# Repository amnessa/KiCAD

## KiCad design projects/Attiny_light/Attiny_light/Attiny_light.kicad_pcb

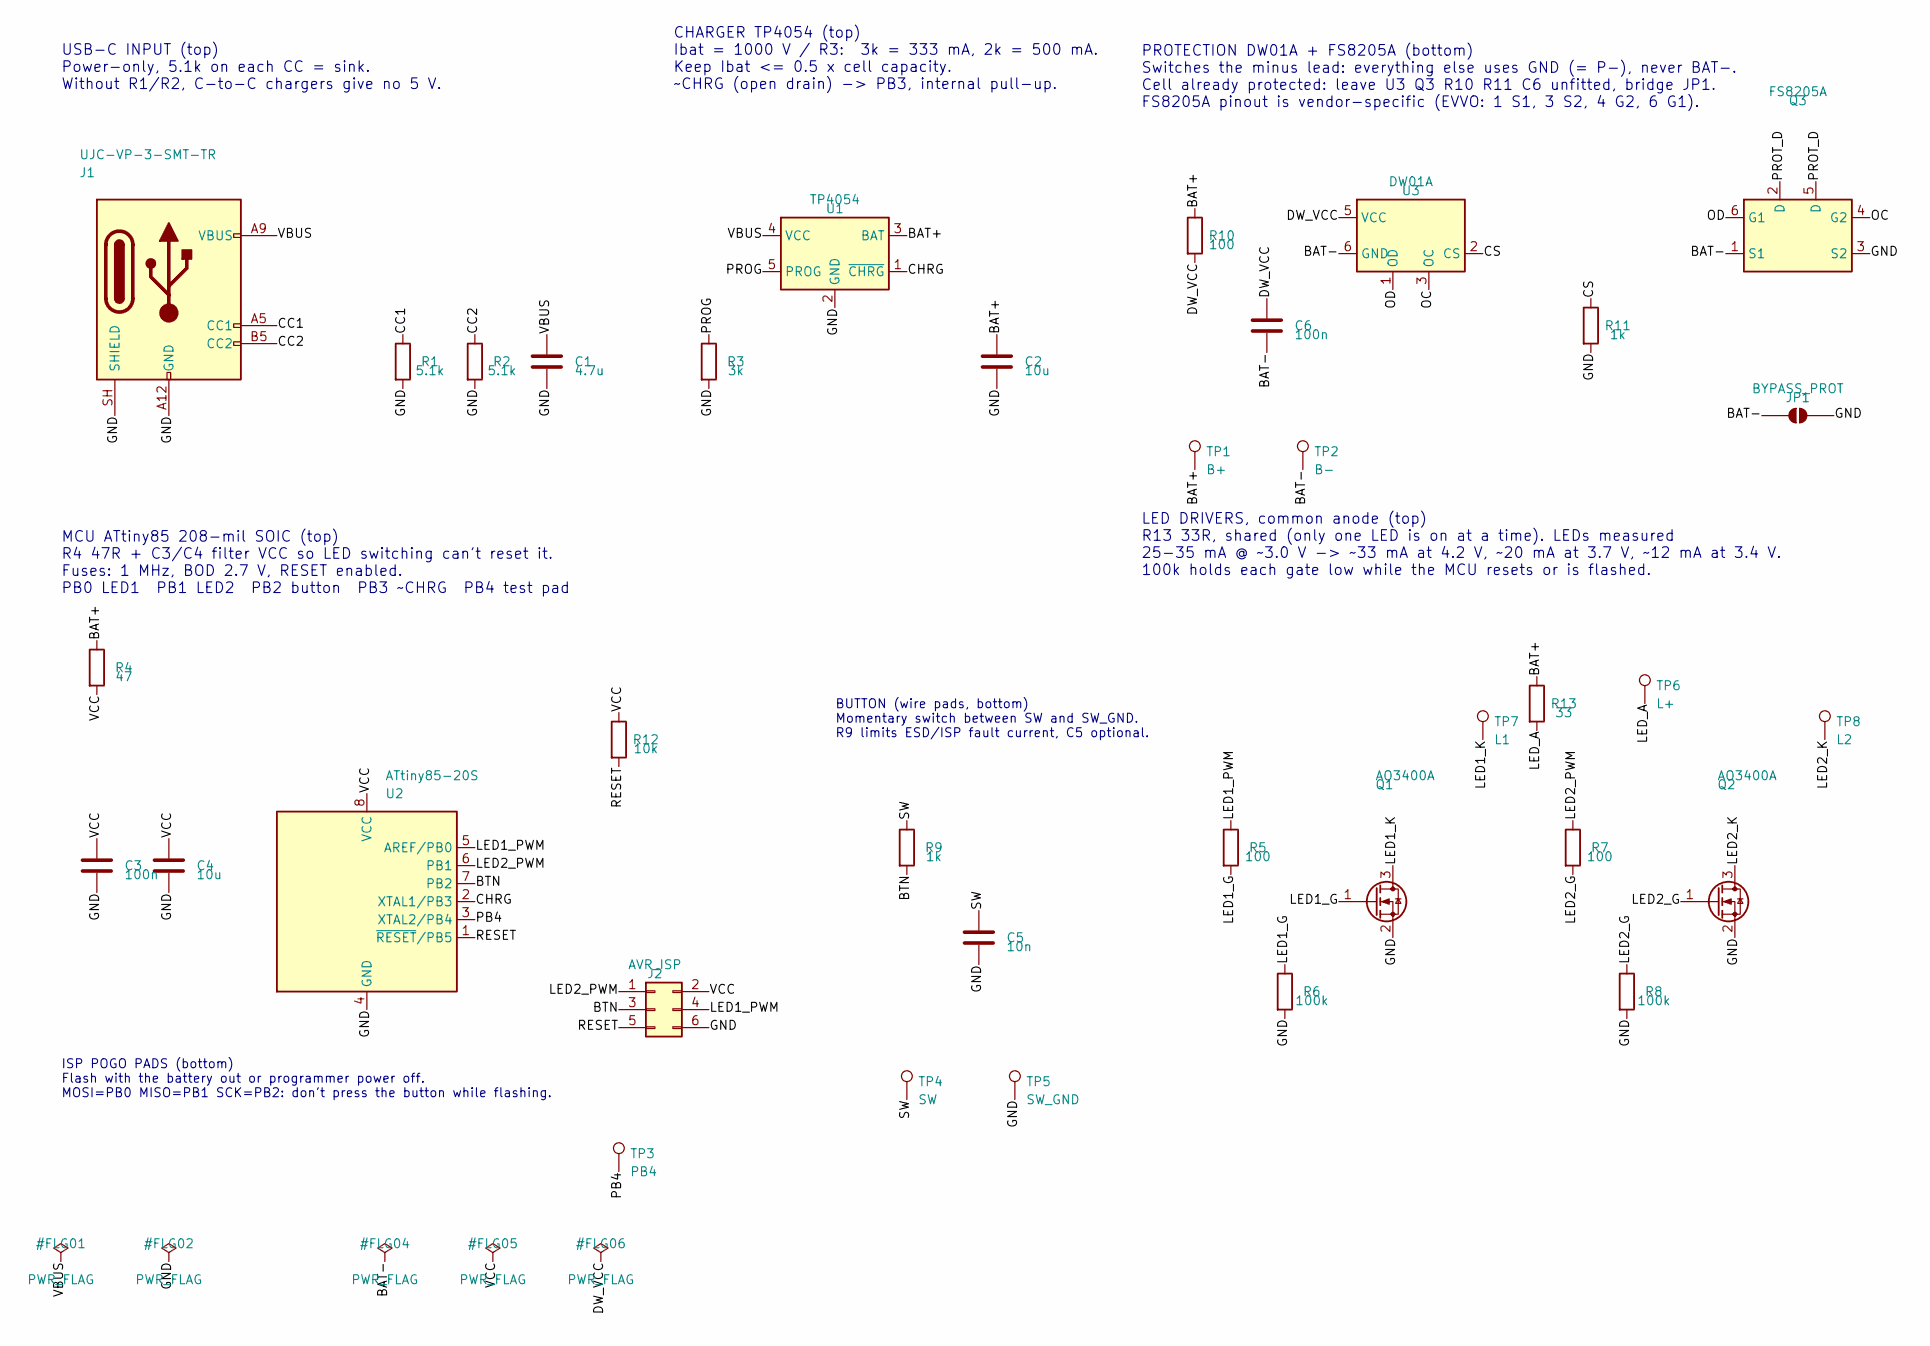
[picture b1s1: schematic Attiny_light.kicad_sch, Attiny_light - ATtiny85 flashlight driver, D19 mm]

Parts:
C1: 4.7u; C_0603_1608Metric
C2, C4: 10u; C_0603_1608Metric
C3, C6: 100n; C_0402_1005Metric
C5: 10n; C_0402_1005Metric
J1: UJC-VP-3-SMT-TR; USB_C_Receptacle_SameSky_UJC-VP-3-SMT_Vertical
J2: AVR_ISP; AVR_ISP_Pogo_2x03_P2.54mm_SMD
JP1: BYPASS_PROT; SolderJumper-2_P1.3mm_Open_RoundedPad1.0x1.5mm
Q1, Q2: AO3400A; SOT-23
Q3: FS8205A; SOT-23-6
R1, R2: 5.1k; R_0402_1005Metric
R3: 3k; R_0402_1005Metric
R4: 47; R_0402_1005Metric
R5, R7, R10: 100; R_0402_1005Metric
R6, R8: 100k; R_0402_1005Metric
R9, R11: 1k; R_0402_1005Metric
R12: 10k; R_0402_1005Metric
R13: 33; R_0603_1608Metric
TP1: B+; TestPoint_Pad_2.0x2.0mm
TP2: B-; TestPoint_Pad_2.0x2.0mm
TP3: PB4; TestPoint_Pad_D1.0mm
TP4: SW; TestPoint_Pad_1.5x1.5mm
TP5: SW_GND; TestPoint_Pad_1.5x1.5mm
TP6: L+; TestPoint_Pad_1.5x1.5mm
TP7: L1; TestPoint_Pad_1.5x1.5mm
TP8: L2; TestPoint_Pad_1.5x1.5mm
U1: TP4054; SOT-23-5
U2: ATtiny85-20S; SOIC-8_5.3x5.3mm_P1.27mm
U3: DW01A; SOT-23-6

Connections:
/BAT+: C2.1, R4.1, R10.1, R13.1, TP1.1, U1.3 (BAT)
/BAT-: C6.2, JP1.1 (A), Q3.1 (S1), TP2.1, U3.6 (GND)
/BTN: J2.3, R9.2, U2.7 (PB2)
/CC1: J1.A5 (CC1), R1.1
/CC2: J1.B5 (CC2), R2.1
/CHRG: U1.1 (~CHRG), U2.2 (XTAL1/PB3)
/CS: R11.1, U3.2 (CS)
/DW_VCC: C6.1, R10.2, U3.5 (VCC)
/GND: C1.2, C2.2, C3.2, C4.2, C5.2, J1.A12 (GND), J1.B12 (GND), J1.SH (SHIELD), J2.6, JP1.2 (B), Q1.2 (S), Q2.2 (S), Q3.3 (S2), R1.2, R2.2, R3.2, R6.2, R8.2, R11.2, TP5.1, U1.2 (GND), U2.4 (GND)
/LED1_G: Q1.1 (G), R5.2, R6.1
/LED1_K: Q1.3 (D), TP7.1
/LED1_PWM: J2.4, R5.1, U2.5 (AREF/PB0)
/LED2_G: Q2.1 (G), R7.2, R8.1
/LED2_K: Q2.3 (D), TP8.1
/LED2_PWM: J2.1, R7.1, U2.6 (PB1)
/LED_A: R13.2, TP6.1
/OC: Q3.4 (G2), U3.3 (OC)
/OD: Q3.6 (G1), U3.1 (OD)
/PB4: TP3.1, U2.3 (XTAL2/PB4)
/PROG: R3.1, U1.5 (PROG)
/PROT_D: Q3.2 (D), Q3.5 (D)
/RESET: J2.5, R12.2, U2.1 (~RESET/PB5)
/SW: C5.1, R9.1, TP4.1
/VBUS: C1.1, J1.A9 (VBUS), J1.B9 (VBUS), U1.4 (VCC)
/VCC: C3.1, C4.1, J2.2, R4.2, R12.1, U2.8 (VCC)

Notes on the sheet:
CHARGER TP4054 (top) Ibat = 1000 V / R3: 3k = 333 mA, 2k = 500 mA. Keep Ibat <= 0.5 x cell capacity. ~CHRG (open drain) -> PB3, internal pull-up.
ISP POGO PADS (bottom) Flash with the battery out or programmer power off. MOSI=PB0 MISO=PB1 SCK=PB2: don't press the button while flashing.
LED DRIVERS, common anode (top) R13 33R, shared (only one LED is on at a time). LEDs measured 25-35 mA @ ~3.0 V -> ~33 mA at 4.2 V, ~20 mA at 3.7 V, ~12 mA at 3.4 V. 100k holds each gate low while the MCU resets or is flashed.
PROTECTION DW01A + FS8205A (bottom) Switches the minus lead: everything else uses GND (= P-), never BAT-. Cell already protected: leave U3 Q3 R10 R11 C6 unfitted, bridge JP1. FS8205A pinout is vendor-specific (EVVO: 1 S1, 3 S2, 4 G2, 6 G1).
MCU ATtiny85 208-mil SOIC (top) R4 47R + C3/C4 filter VCC so LED switching can't reset it. Fuses: 1 MHz, BOD 2.7 V, RESET enabled. PB0 LED1 PB1 LED2 PB2 button PB3 ~CHRG PB4 test pad
BUTTON (wire pads, bottom) Momentary switch between SW and SW_GND. R9 limits ESD/ISP fault current, C5 optional.
USB-C INPUT (top) Power-only, 5.1k on each CC = sink. Without R1/R2, C-to-C chargers give no 5 V.

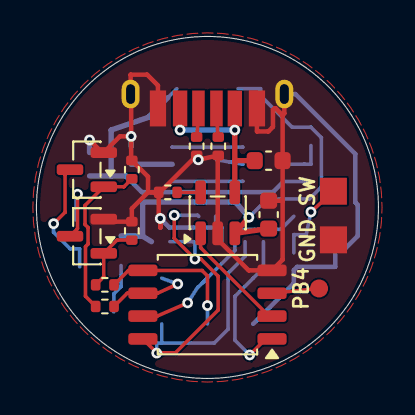
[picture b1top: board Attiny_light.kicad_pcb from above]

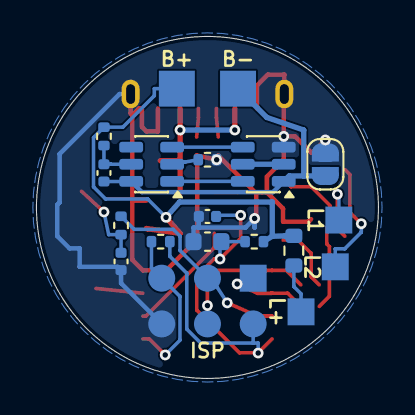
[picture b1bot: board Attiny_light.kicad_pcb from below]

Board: 2 copper layers, 19.0 x 19.0 mm, 36 parts (19 on the bottom side), 25 nets.

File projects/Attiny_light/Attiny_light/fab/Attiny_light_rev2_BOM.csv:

"Refs","Value","Footprint","Qty"
"C1","4.7u","Capacitor_SMD:C_0603_1608Metric","1"
"C2,C4","10u","Capacitor_SMD:C_0603_1608Metric","2"
"C3,C6","100n","Capacitor_SMD:C_0402_1005Metric","2"
"C5","10n","Capacitor_SMD:C_0402_1005Metric","1"
"J1","UJC-VP-3-SMT-TR","Attiny_light:USB_C_Receptacle_SameSky_UJC-VP-3-SMT_Vertical","1"
"Q1,Q2","AO3400A","Package_TO_SOT_SMD:SOT-23","2"
"Q3","FS8205A","Package_TO_SOT_SMD:SOT-23-6","1"
"R1,R2","5.1k","Resistor_SMD:R_0402_1005Metric","2"
"R3","3k","Resistor_SMD:R_0402_1005Metric","1"
"R4","47","Resistor_SMD:R_0402_1005Metric","1"
"R5,R7,R10","100","Resistor_SMD:R_0402_1005Metric","3"
"R6,R8","100k","Resistor_SMD:R_0402_1005Metric","2"
"R9,R11","1k","Resistor_SMD:R_0402_1005Metric","2"
"R12","10k","Resistor_SMD:R_0402_1005Metric","1"
"R13","33","Resistor_SMD:R_0603_1608Metric","1"
"U1","TP4054","Package_TO_SOT_SMD:SOT-23-5","1"
"U2","ATtiny85-20S","Package_SO:SOIC-8_5.3x5.3mm_P1.27mm","1"
"U3","DW01A","Package_TO_SOT_SMD:SOT-23-6","1"

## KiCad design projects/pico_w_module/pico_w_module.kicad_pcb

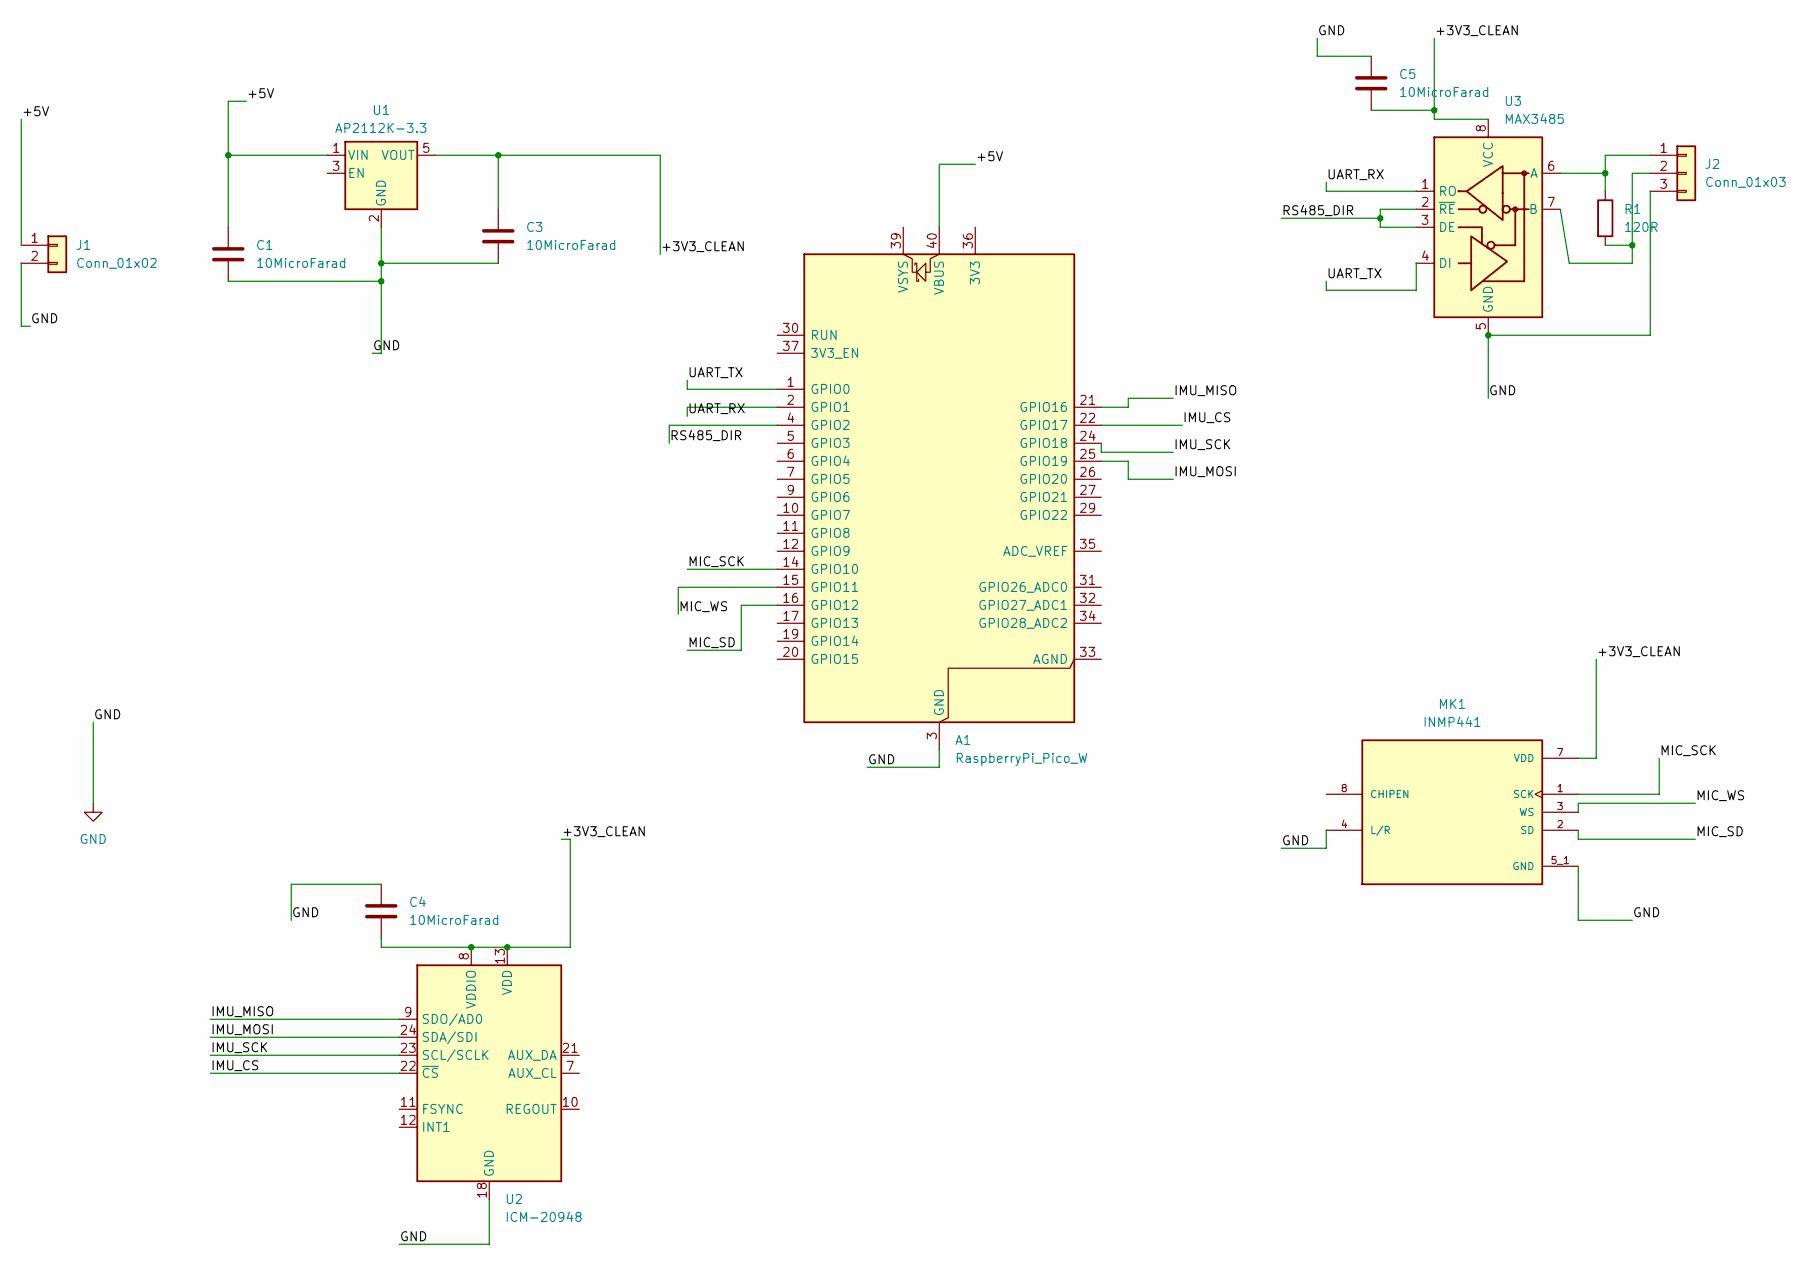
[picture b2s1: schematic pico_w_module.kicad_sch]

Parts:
A1: RaspberryPi_Pico_W; RaspberryPi_Pico_W_SMD_HandSolder
C1, C3, C4, C5: 10MicroFarad; C_0805_2012Metric_Pad1.18x1.45mm_HandSolder
J1: Conn_01x02; PinSocket_1x02_P2.54mm_Horizontal
J2: Conn_01x03; PinSocket_1x03_P2.54mm_Horizontal
MK1: INMP441; MIC_INMP441; PARTREV 1.1
R1: 120R; C_1206_3216Metric_Pad1.33x1.80mm_HandSolder
U1: AP2112K-3.3; SOT-23-5
U2: ICM-20948; InvenSense_QFN-24_3x3mm_P0.4mm
U3: MAX3485; SOIC-8_3.9x4.9mm_P1.27mm

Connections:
/+3V3_CLEAN: C3.1, C4.2, C5.2, MK1.7 (VDD), U1.5 (VOUT), U2.8 (VDDIO), U2.13 (VDD), U3.8 (VCC)
/+5V: A1.40 (VBUS), C1.1, J1.1, U1.1 (VIN)
/IMU_CS: A1.22 (GPIO17), U2.22 (~CS)
/IMU_MISO: A1.21 (GPIO16), U2.9 (SDO/AD0)
/IMU_MOSI: A1.25 (GPIO19), U2.24 (SDA/SDI)
/IMU_SCK: A1.24 (GPIO18), U2.23 (SCL/SCLK)
/MIC_SCK: A1.14 (GPIO10), MK1.1 (SCK)
/MIC_SD: A1.16 (GPIO12), MK1.2 (SD)
/MIC_WS: A1.15 (GPIO11), MK1.3 (WS)
/RS485_DIR: A1.4 (GPIO2), U3.2 (~RE), U3.3 (DE)
/UART_RX: A1.2 (GPIO1), U3.1 (RO)
/UART_TX: A1.1 (GPIO0), U3.4 (DI)
GND: A1.3 (GND), A1.8 (GND), A1.13 (GND), A1.18 (GND), A1.23 (GND), A1.28 (GND), A1.38 (GND), C1.2, C3.2, C4.1, C5.1, J1.2, J2.3, MK1.4 (L/R), MK1.5_1 (GND), MK1.5_2 (GND), MK1.6 (GND), MK1.9 (GND), U1.2 (GND), U2.18 (GND), U2.20 (GND), U3.5 (GND)
unnamed: J2.1, R1.1, U3.6 (A)
unnamed: J2.2, R1.2, U3.7 (B)

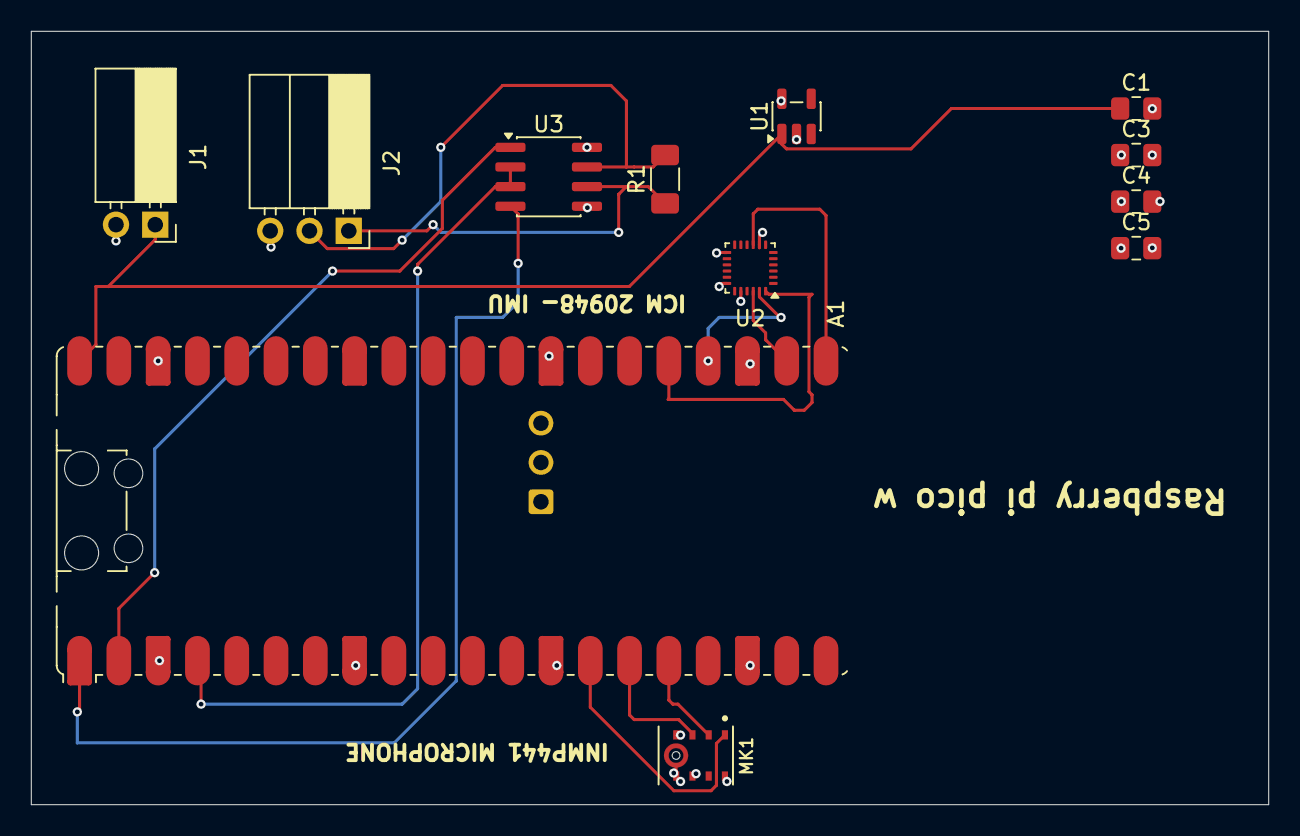
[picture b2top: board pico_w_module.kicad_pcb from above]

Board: 4 copper layers, 80.0 x 50.0 mm, 12 parts (0 on the bottom side), 15 nets.

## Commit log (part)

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2026-04-03 first commit project welding cell
2026-04-04 conceptual version
2026-04-04 conception version complete
2026-04-12 attiny prject started
2026-04-14 attiny progress to the 3d
